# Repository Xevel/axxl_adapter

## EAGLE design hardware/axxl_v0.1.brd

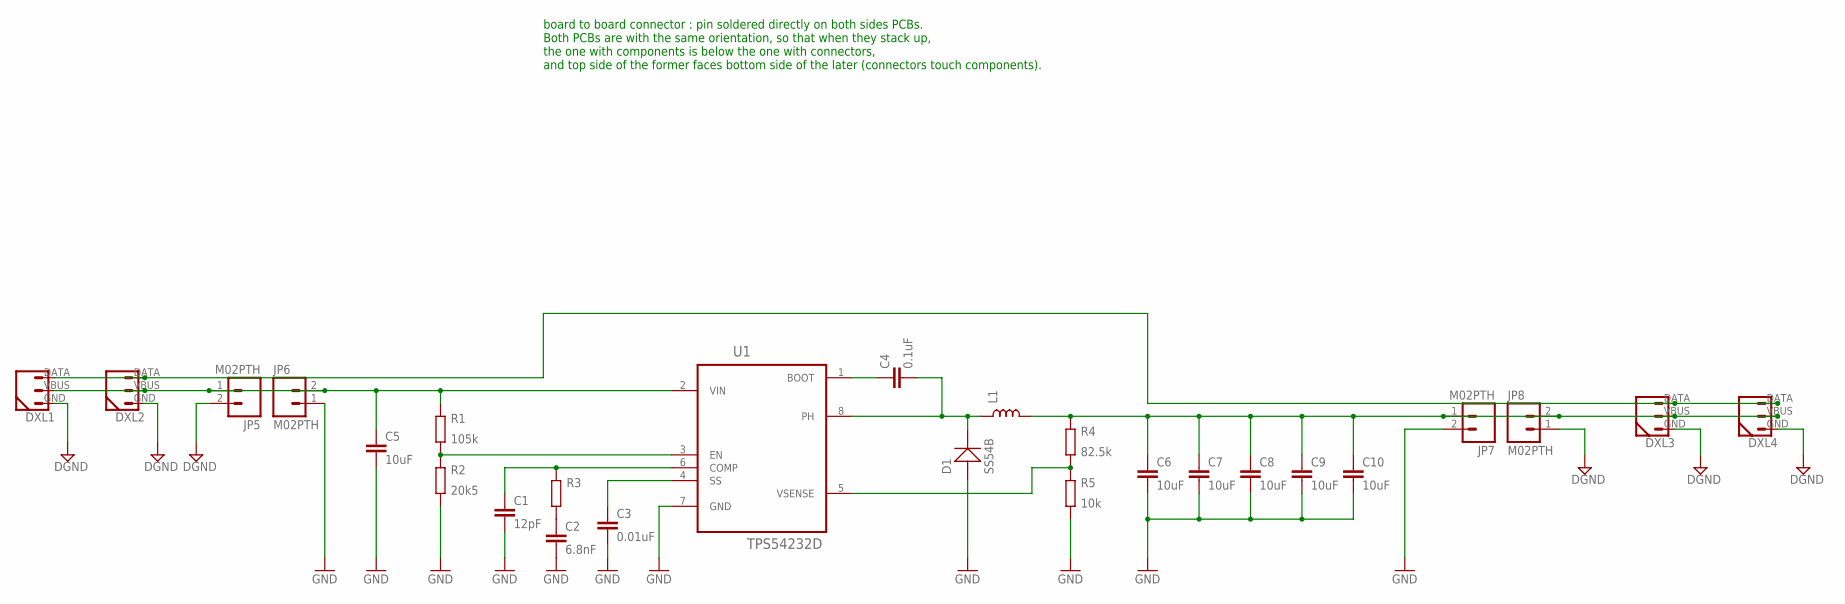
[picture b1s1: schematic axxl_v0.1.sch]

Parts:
C1: 12pF; 0402_N
C2: 6.8nF; 0402_N
C3: 0.01uF; 0402_N
C4: 0.1uF; 0402_N
C5, C6, C7, C8, C9, C10: 10uF; 0805_N
D1: SS54B; SMB
DXL1, DXL2: DYNAMIXEL_3POS-R; DYNAMIXEL_3POS_RIGHT
DXL3, DXL4: DYNAMIXEL_3POS-XL-R; DYNAMIXEL_XL_RIGHT
JP5, JP6, JP7, JP8: M02PTH; 1X02
L1: L-SMD_8X8; L_SRU8043
R1: 105k; 0402_N
R2: 20k5; 0402_N
R3: R0402; 0402_N
R4: 82.5k; 0402_N
R5: 10k; 0402_N
U1: TPS54232D; SOIC127P600X175-8N

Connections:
DGND: DXL1.GND (1), DXL2.GND (1), DXL3.GND (1), DXL4.GND (1), JP5.2, JP8.1
GND: C1.2, C2.2, C3.2, C5.2, C6.2, C7.2, C8.2, C9.2, C10.2, D1.+, JP6.1, JP7.2, R2.1, R5.1, U1.7 (GND)
unnamed: C1.1, R3.2, U1.6 (COMP)
unnamed: C6.1, C7.1, C8.1, C9.1, C10.1, DXL3.VBUS (2), DXL4.VBUS (2), JP7.1, JP8.2, L1.P$2 (2), R4.2
unnamed: R1.1, R2.2, U1.3 (EN)
unnamed: C2.1, R3.1
unnamed: C3.1, U1.4 (SS)
unnamed: C4.1, U1.1 (BOOT)
unnamed: C4.2, D1.-, L1.P$1 (1), U1.8 (PH)
unnamed: DXL1.DATA (3), DXL2.DATA (3), DXL3.DATA (3), DXL4.DATA (3)
unnamed: R4.1, R5.2, U1.5 (VSENSE)
unnamed: C5.1, DXL1.VBUS (2), DXL2.VBUS (2), JP5.1, JP6.2, R1.2, U1.2 (VIN)

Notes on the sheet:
board to board connector : pin soldered directly on both sides PCBs. Both PCBs are with the same orientation, so that when they stack up, the one with components is below the one with connectors, and top side of the former faces bottom side of the later (connectors touch components).

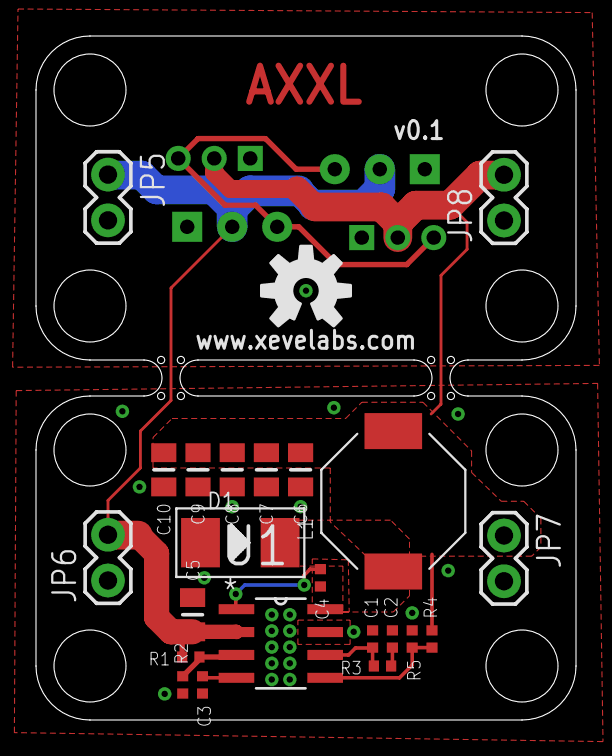
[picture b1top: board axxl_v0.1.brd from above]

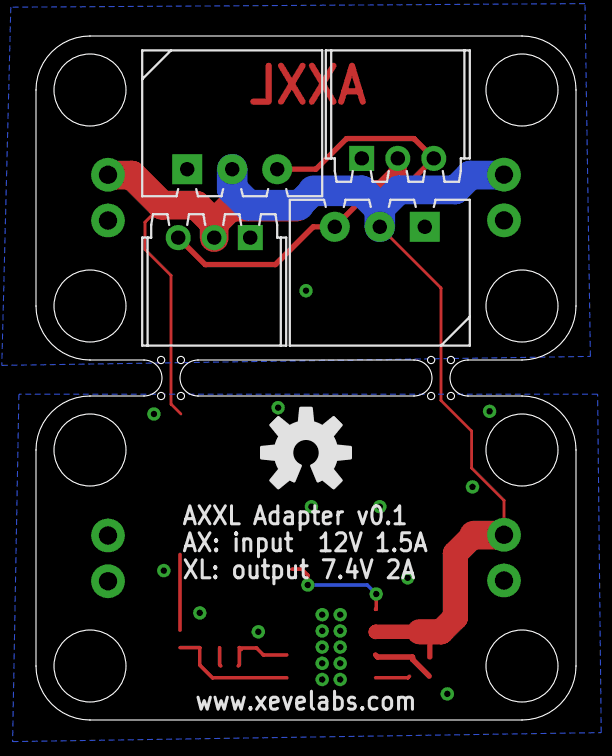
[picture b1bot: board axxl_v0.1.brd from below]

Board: 2 copper layers, 30.0 x 38.0 mm, 28 parts (5 on the bottom side), 12 nets.

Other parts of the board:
U$1, U$2: OSHW-LOGO-M

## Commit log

2014-09-18 First proto of AXXL adapter (v0.1). It's made as a two-board stack but grouped into one to lower prototyping cost.

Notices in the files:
parts and their libraries:
SparkFun-Aesthetics: Licensing: CC v3.0 Share-Alike You are welcome to use this library for commercial purposes.
